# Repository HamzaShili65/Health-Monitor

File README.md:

<h1> Heart Rate & Temperature Sensing Module</h1>

<p> A heart rate sensor that measures BPM and SPO2 and a temperature and humidity sensor. All data are displayed on the TFT touchscreen.</p>

**Background and Motivation:** <br>
The project is a combination of a heart rate sensor, a temperature and humidity sensor, and an LCD screen. The GY-MAX30102 heart rate sensor uses photoplethysmography - shining light on the skin to measure the perfusion of the blood in an artery - to measure a person's heart rate in beats per minute (BMP) and the level of Oxygen in blood SPO2 in percentage (%). The BMP 280 sensor measures temperature and humidity in the room. The data generated from both sensors are displayed on an LCD 2.8" screen for the person using the device to see them.<br>
<br>
My college life inspired me to create this project. As someone who's not used to Houston's weather and high level of humidity, I always wanted a way to measure temperature and humidity inside my room so that I can see if my AC is displaying the right temperature or not. Moreover, given the level of academic stress that college students go through, I thought it would be useful to have an accessible heart rate sensor to monitor how stress is affecting my heart beats.<br>
<br>
**project HackSter Link:** https://www.hackster.io/hamzashili/heart-rate-temperature-sensing-module-86caaf

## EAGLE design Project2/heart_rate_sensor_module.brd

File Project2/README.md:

Please read this for information about the directory!

This directory contains the files (library, board, schematics, manufacturing, bill of materials, etc) for a custom PCB design for my heart rate module project. If you want to learn more about the porject please visit the following hackster page: https://www.hackster.io/hamzashili/heart-rate-temperature-sensing-module-86caaf.

The PCB was designed using EAGLE and the top and bottom layer photos were obtained from Gerbv.

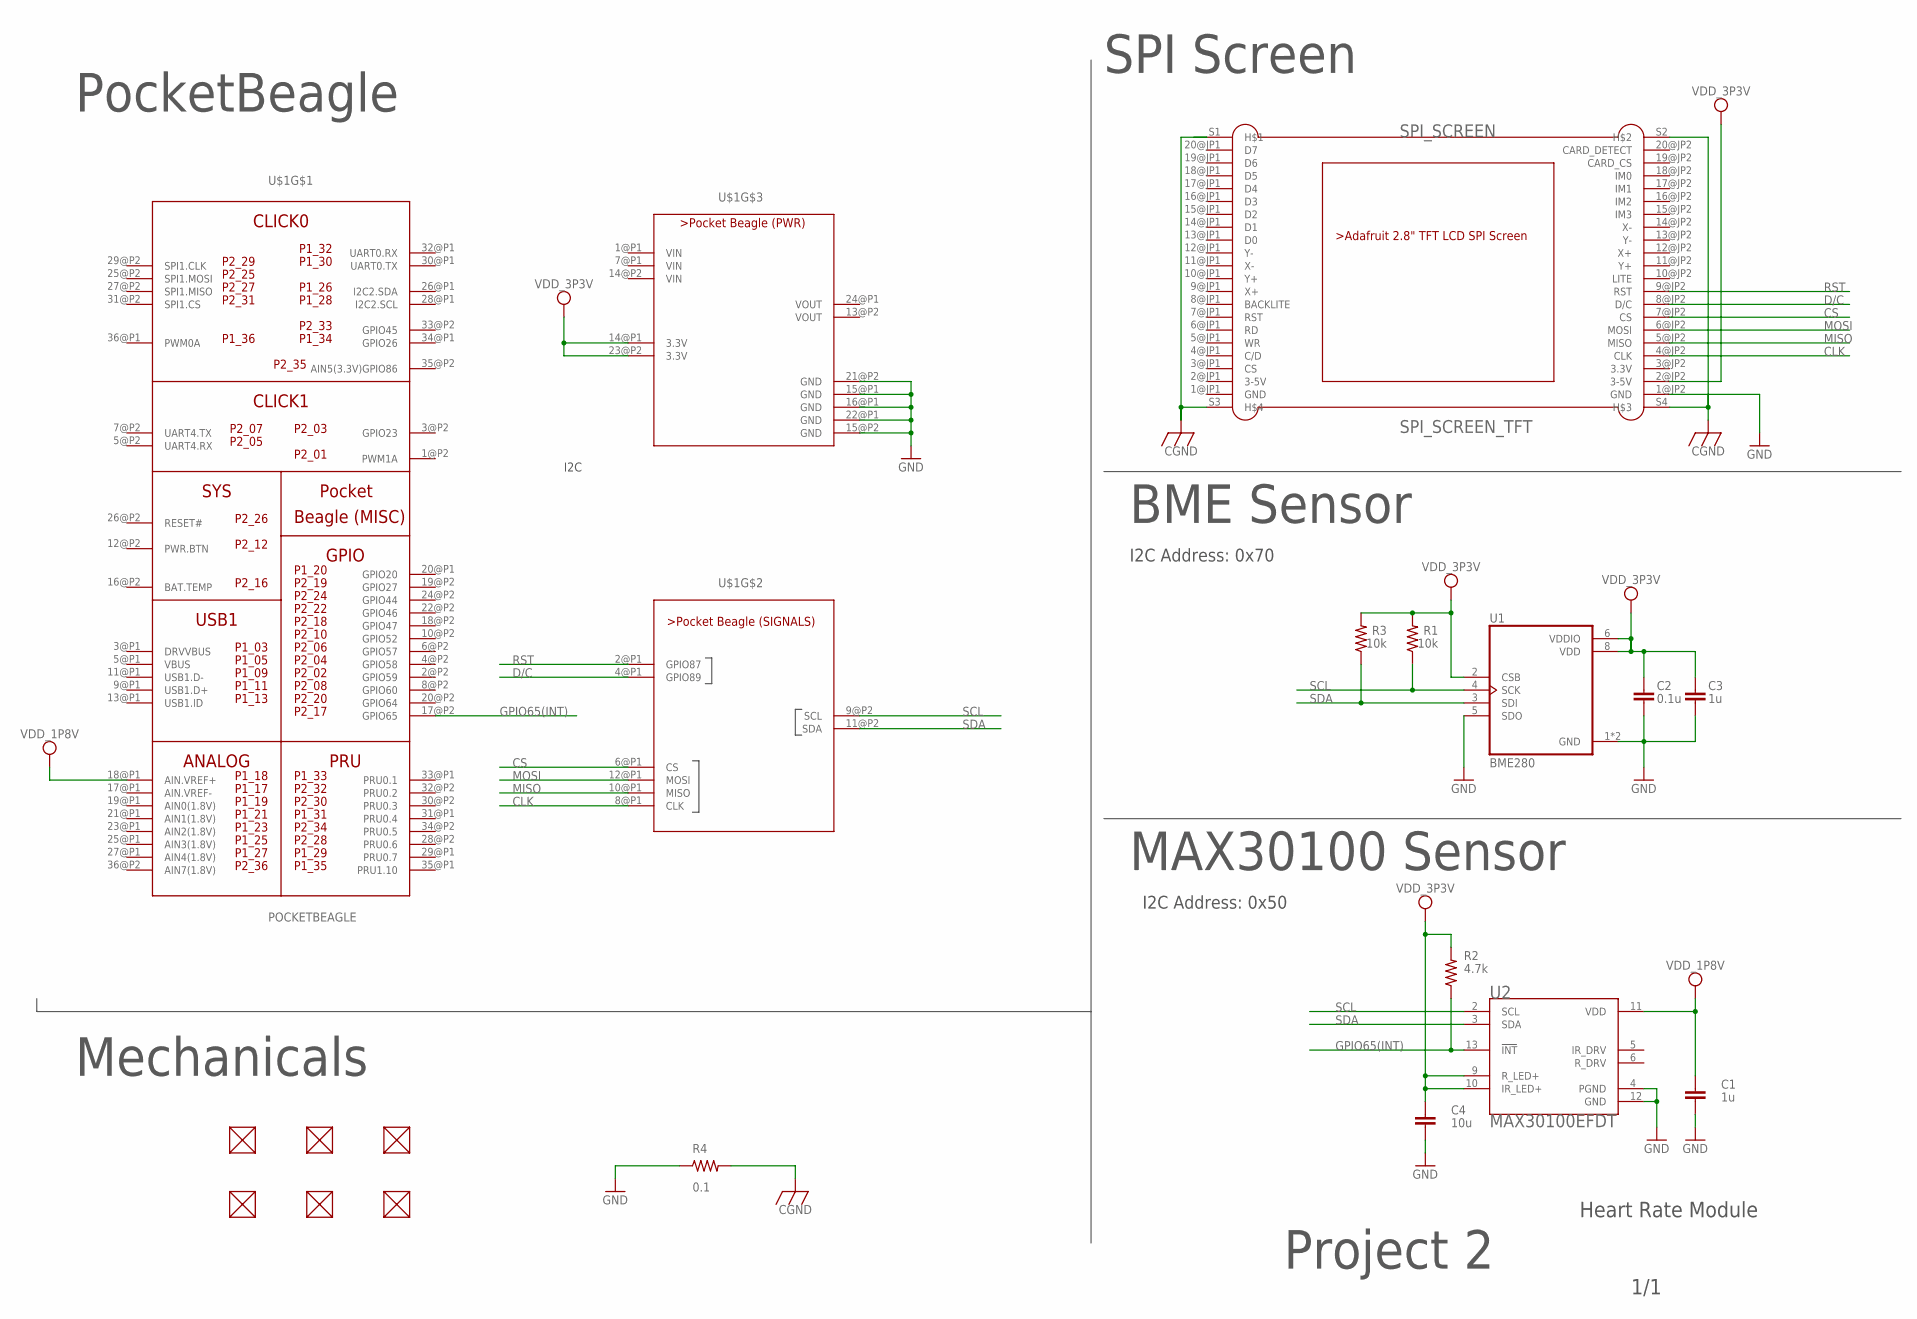
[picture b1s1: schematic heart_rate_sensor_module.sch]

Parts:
C1, C3: 1u; C0603
C2: 0.1u; C0603
C4: 10u; C0603
FUD1, FUD2, FUD3, FUD4, FUD5, FUD6: FIDUCIAL; FIDUCIAL_40MIL
R1, R3: 10k; R0603
R2: 4.7k; R0603
R4: 0.1; R0805
SPI_SCREEN: SPI_SCREEN_TFT; SPI_SREEN_TFT
U1: BME280; PSON65P250X250X100-8N
U2: MAX30100EFDT; LGA14R80P2X7_560X280X130
U$1: POCKETBEAGLE

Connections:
CGND: R4.2, SPI_SCREEN.S1, SPI_SCREEN.S2, SPI_SCREEN.S3, SPI_SCREEN.S4
CLK: SPI_SCREEN.4@JP2 (CLK), U$1.8@P1 (CLK)
CS: SPI_SCREEN.7@JP2 (CS), U$1.6@P1 (CS)
D/C: SPI_SCREEN.8@JP2 (D/C), U$1.4@P1 (GPIO89)
GND: C1.2, C2.2, C3.2, C4.2, R4.1, SPI_SCREEN.1@JP2 (GND), U1.1 (GND), U1.5 (SDO), U1.7 (GND), U2.4 (PGND), U2.12 (GND), U$1.15@P1 (GND), U$1.15@P2 (GND), U$1.16@P1 (GND), U$1.21@P2 (GND), U$1.22@P1 (GND)
GPIO65(INT): R2.1, U2.13 (!INT), U$1.17@P2 (GPIO65)
MISO: SPI_SCREEN.5@JP2 (MISO), U$1.10@P1 (MISO)
MOSI: SPI_SCREEN.6@JP2 (MOSI), U$1.12@P1 (MOSI)
RST: SPI_SCREEN.9@JP2 (RST), U$1.2@P1 (GPIO87)
SCL: R1.1, U1.4 (SCK), U2.2 (SCL), U$1.9@P2 (SCL)
SDA: R3.1, U1.3 (SDI), U2.3 (SDA), U$1.11@P2 (SDA)
VDD_1P8V: C1.1, U2.11 (VDD), U$1.18@P1 (AIN.VREF+)
VDD_3P3V: C2.1, C3.1, C4.1, R1.2, R2.2, R3.2, SPI_SCREEN.2@JP2 (3-5V), U1.2 (CSB), U1.6 (VDDIO), U1.8 (VDD), U2.9 (R_LED+), U2.10 (IR_LED+), U$1.14@P1 (3.3V), U$1.23@P2 (3.3V)

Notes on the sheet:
PocketBeagle
Mechanicals
SPI Screen
BME Sensor
I2C
MAX30100 Sensor
I2C Address: 0x50
Project 2
Heart Rate Module
1/1
I2C Address: 0x70

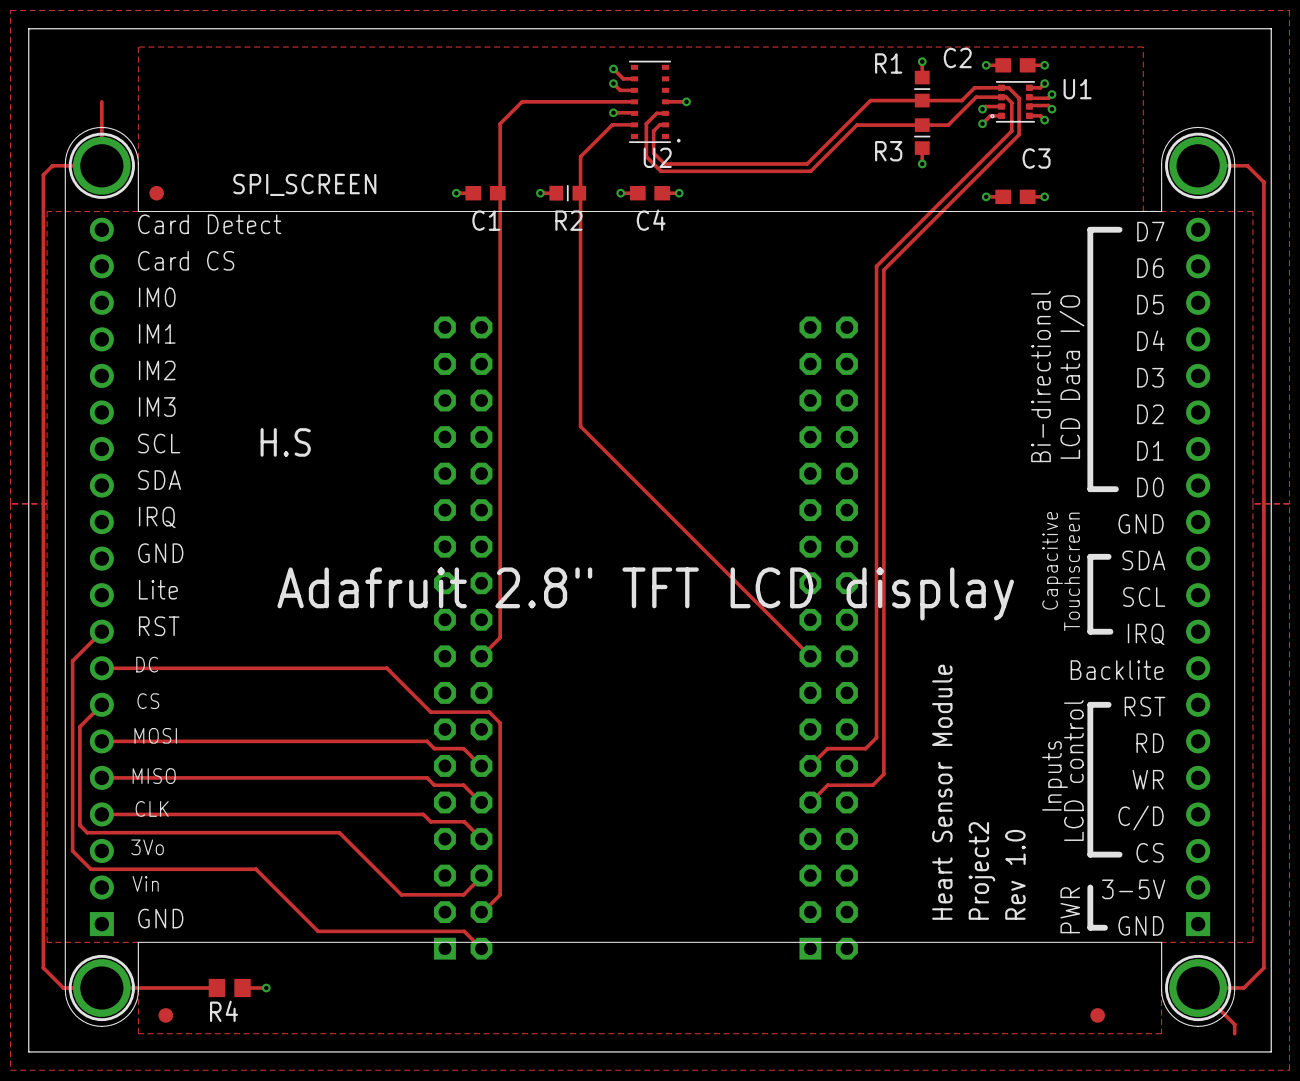
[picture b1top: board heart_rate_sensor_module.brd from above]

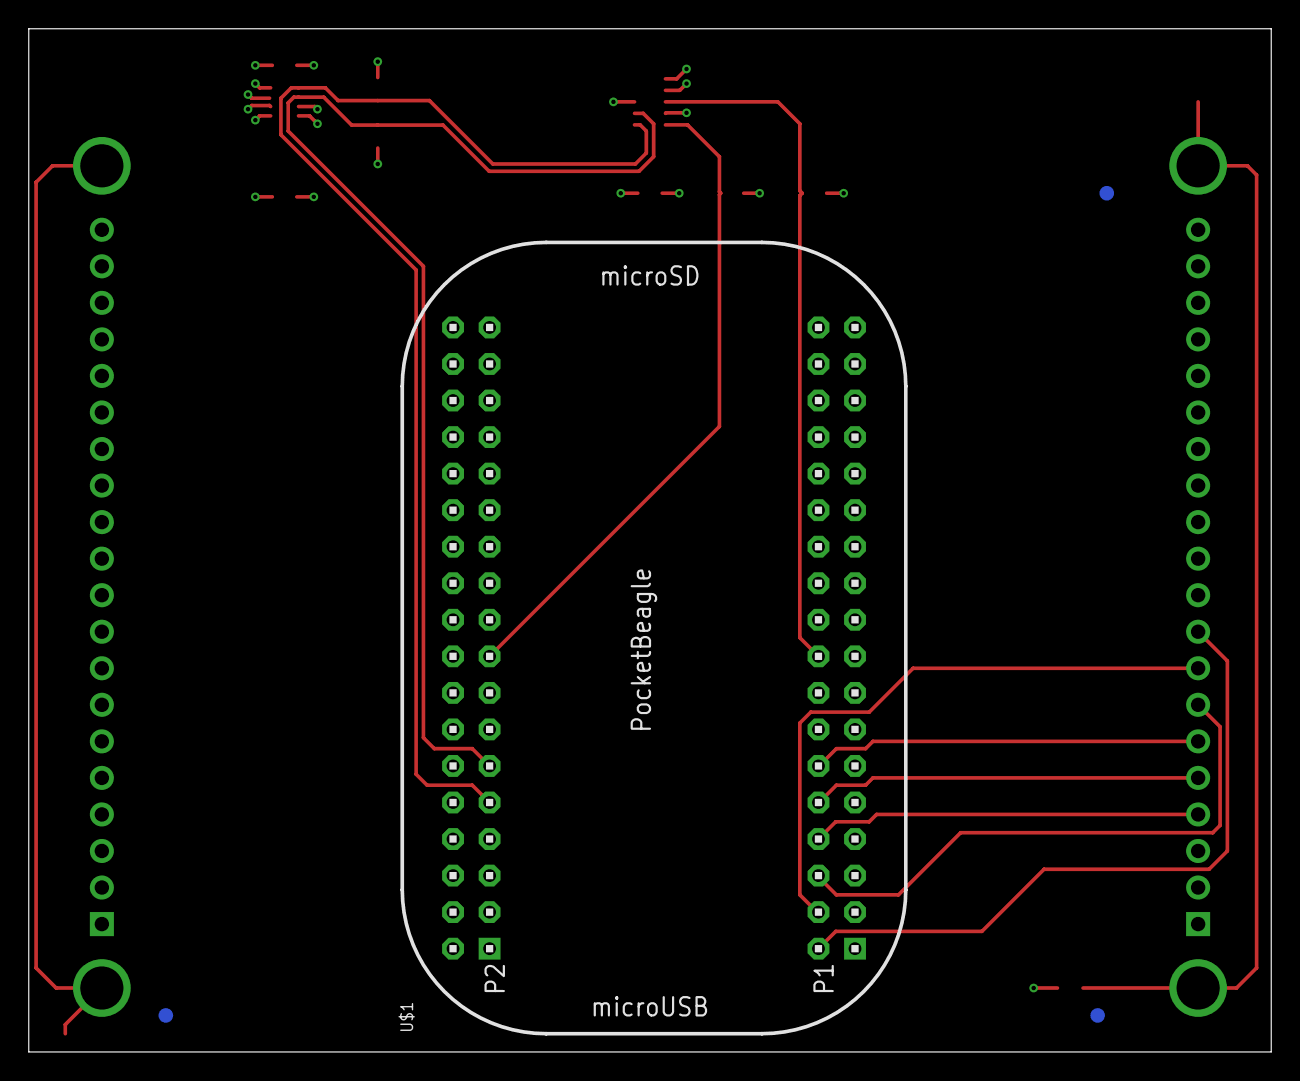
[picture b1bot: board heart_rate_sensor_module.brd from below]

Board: 4 copper layers, 86.4 x 71.1 mm, 18 parts (4 on the bottom side), 13 nets.

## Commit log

2022-02-16 "HW4_Q1_Calculator"
2022-02-16 "HW4_Q1_Latestversion
2022-02-16 "HW4_Q2"
